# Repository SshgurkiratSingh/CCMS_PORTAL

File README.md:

# CCMS Portal — Centralized Command & Monitoring System

A full-stack smart streetlight fleet management system with real-time monitoring, remote control, and analytics. This monorepo contains the Next.js operator console, native Android mobile application, AWS Lambda backend, ESP32 firmware for edge devices, and PCB designs.

## Screenshots & Assets

| Fleet Info | Node Info | Command Menu |
|:---:|:---:|:---:|
|  |  |  |

| Prototype | Power Supply Unit | Offsite Interface Card |
|:---:|:---:|:---:|
|  |  |  |

---

## Architecture Overview

```text
┌──────────────────┐       ┌──────────────┐       ┌─────────────────┐
│ RPi Gateway + STM│──────▶│   AWS IoT    │──────▶│  SQS → Lambda   │──────▶ DynamoDB
│  (streetlights)  │  MQTT │   Core       │       │ (saveDataFromSQ)│
└──────────────────┘       └──────────────┘       └─────────────────┘
                                                          │
                                                          ▼
┌──────────────────┐       ┌──────────────┐       ┌─────────────────┐
│   Next.js App    │◀──────│   Lambda     │◀──────│  DynamoDB       │
│  (operator       │  REST │   API        │       │                 │
│   console)       │       │   Gateway    │       │                 │
└──────────────────┘       └──────────────┘       └─────────────────┘
         ▲                        ▲
         │                        │
         └─────────┬──────────────┘
                   │ REST (x-dashboard-key / x-admin-key)
                   ▼
        ┌────────────────────┐
        │    Android App     │
        │  (CCMS Mobile Console)│
        └────────────────────┘
```

### Components

| Layer                             | Technology                            | Location                                                         |
| --------------------------------- | ------------------------------------- | ---------------------------------------------------------------- |
| **Web Portal**                    | Next.js 16, React 19, Tailwind CSS v4 | [`Frontend/ccms/`](./Frontend/ccms)                              |
| **Android App**                   | Kotlin, Jetpack Compose, Material 3, Retrofit | [`androidAPp/`](./androidAPp)                             |
| **Backend API**                   | Python AWS Lambda                     | [`Backend/Lambda/`](./Backend/Lambda)                            |
| **Firmware (RPi Gateway)**        | Python 3                              | [`Firmware/RPi_Gateway/`](./Firmware/RPi_Gateway)                |
| **Firmware (STM32 Node)**         | C++ (PlatformIO), STM32               | [`Firmware/STM32_Peripheral/`](./Firmware/STM32_Peripheral)      |
| **Firmware v2.0**                 | C++ (PlatformIO), ESP32               | [`Firmware/ESP32_wifi_CCMS_v2.0/`](./Firmware/ESP32_wifi_CCMS_v2.0) |
| **Firmware v2.0 (Pi link)**       | C++ (PlatformIO), ESP32               | [`Firmware/ESP32_wifi_CCMS_v2.0_PI_link/`](./Firmware/ESP32_wifi_CCMS_v2.0_PI_link) |
| **Firmware v1.0**                 | C++ (PlatformIO), ESP32               | [`Firmware/ESP32_wifi_CCMS_v1.0/`](./Firmware/ESP32_wifi_CCMS_v1.0) |
| **Hardware**                      | PCB Designs                           | [`Hardware/PCB Designs/`](./Hardware/PCB%20Designs)              |
| **Documentation**                 | MkDocs (Material theme)               | [`docs/`](./docs), [`mkdocs.yml`](./mkdocs.yml)                  |

---

## Android App — Mobile Command Console (`androidAPp/`)

A high-performance Android mobile application built with **Kotlin** and **Jetpack Compose (Material 3)** for real-time fleet monitoring, remote relay dispatch, and telemetry analytics.

### Key Features

- 📊 **Command Center Dashboard**: Fleet-wide HUD showing active nodes, active alarms, grid voltage ($V$), frequency ($Hz$), system power factor ($PF$), and instantaneous load ($kW$).
- ⚡ **Node Fleet Browser**: Filter and search panels by Panel ID, location, or MAC address with direct relay switch toggling and optimistic UI state updates.
- 🔍 **Live Schneider Modbus Telemetry**: Real-time readout of Schneider Electric energy meter registers (`R3027`, `R3035`, `R3109`, `R3059`, `R3053`, `R3009`, `R3083`), diagnostic battery voltage, mains status, and enclosure temperature.
- 🚨 **Automated Telemetry Fault Detection Engine**: Runs 6 continuous telemetry analysis rules:
  - **E001**: Sustained Low Voltage ($< 200\text{V}$)
  - **E002**: Sustained High Voltage Spike ($> 250\text{V}$)
  - **E003**: Power Factor Degradation ($< 0.75$)
  - **E004**: Grid Frequency Instability ($< 49.5\text{Hz}$ or $> 50.5\text{Hz}$)
  - **E006/E007**: Temperature Breach ($> 50^\circ\text{C}$ or $> 65^\circ\text{C}$)
  - **E008**: Enclosure Tamper / Tilt Switch Triggered
- 🗺️ **Map Location Integration**: Tap location pins to launch Google Maps pointing to exact GPS coordinates ($30.7356^\circ\text{N}, 76.7105^\circ\text{E}$).
- 📈 **Interactive Telemetry Line Charts**: Canvas-drawn time-series graphs with touch cursor inspection and range selectors (1h, 6h, 24h, 7d).
- ⚙️ **Dual-Key API Gateway Config**: Configure AWS Lambda endpoint, Level 1 Dashboard key (`x-dashboard-key`), Level 2 Admin key (`x-admin-key`), and toggle offline simulator mode.

### Tech Stack

- **Language**: Kotlin 2.2
- **UI Framework**: Jetpack Compose, Material 3, Navigation Compose
- **Networking**: Retrofit 2.11, OkHttp 4.12, Gson
- **Async State**: Kotlin Coroutines, StateFlow, ViewModel
- **Theme**: High-contrast Cyber Command Slate palette with Frosted Glassmorphism (`GlassCard`)

### Build & Export APK

```bash
cd androidAPp
./gradlew app:assembleDebug app:assembleRelease
```

#### Generated APK Paths

- **Debug APK**: [`androidAPp/app/build/outputs/apk/debug/app-debug.apk`](file:///home/gurkirat/Projects/CCMS_PORTAL/androidAPp/app/build/outputs/apk/debug/app-debug.apk)
- **Release APK**: [`androidAPp/app/build/outputs/apk/release/app-release-unsigned.apk`](file:///home/gurkirat/Projects/CCMS_PORTAL/androidAPp/app/build/outputs/apk/release/app-release-unsigned.apk)

---

## Frontend — Operator Console (`Frontend/ccms/`)

A Next.js static export application that provides a real-time operations dashboard for managing streetlight fleets.

### Pages

| Route                   | Description                                                                    |
| ----------------------- | ------------------------------------------------------------------------------ |
| `/`                   | Landing page with login / dashboard links                                      |
| `/login`              | Authenticate using Dashboard Key and Admin Key                                 |
| `/dashboard`          | Fleet-wide summary (panel count, active alarms, grid metrics, energy estimate) |
| `/panels`             | Browse, filter, and search all panels (map + list views)                       |
| `/panel?id={panelId}` | Live status, telemetry charts, command dispatch (relay, schedule, shadow keys) |
| `/manage-panel`       | Register new panels with GPS coordinates                                       |
| `/analytics`          | Historical telemetry viewer with date range filtering                          |
| `/alerts`             | Active alerts list with severity filtering and acknowledgment                  |

### Key Technologies

- **Framework**: Next.js 16 (`output: "export"` — fully static, no server functions)
- **UI Library**: HeroUI v3, Lucide icons
- **Charts**: Recharts (telemetry time-series)
- **Maps**: Leaflet + React-Leaflet (panel fleet locations, location picker)
- **Styling**: Tailwind CSS v4, Framer Motion (animations)
- **Auth**: API keys stored in `localStorage`, sent as `x-dashboard-key` / `x-admin-key` headers

### Environment Variables

```env
NEXT_PUBLIC_API_BASE_URL=https://85siwerqrg.execute-api.us-east-1.amazonaws.com/default/
```

Copy `Frontend/ccms/.env.example` → `Frontend/ccms/.env.local` and fill in real values.

### Run Locally

```bash
cd Frontend/ccms
npm install
npm run dev       # development server at http://localhost:3000
npm run build     # static export to Frontend/ccms/out/
```

---

## Backend — AWS Lambda (`Backend/Lambda/`)

Python-based serverless functions deployed behind API Gateway.

### Functions

| File                                                         | Purpose                                                                            |
| ------------------------------------------------------------ | ---------------------------------------------------------------------------------- |
| [`lambdaAPI.py`](./Backend/Lambda/lambdaAPI.py)                       | REST API handler — serves dashboard snapshot, panel status, history, and commands |
| [`saveDataFromSQStoDB,py`](./Backend/Lambda/saveDataFromSQStoDB,py) | SQS-triggered function that writes incoming telemetry to DynamoDB                  |

### API Endpoints (via `DashboardAPIHandler`)

| Method    | Query / Body                                             | Description                                      |
| --------- | -------------------------------------------------------- | ------------------------------------------------ |
| `GET`   | `?enquiry=snapshot`                                    | Returns all panels with latest data and metadata |
| `GET`   | `?enquiry=history&panel_id=X&start=T&end=T`            | Historical telemetry for a panel                 |
| `POST`  | `{ panel_id, ... }`                                    | Register a new panel                             |
| `PATCH` | `{ panel_id, desired_state/schedule/shadowKeys, ... }` | Send commands to a panel                         |

### Test Endpoints

A Node.js test script is available at [`Backend/Lambda/TestEndpoints/getData.js`](./Backend/Lambda/TestEndpoints/getData.js) for manual API testing.

---

## Hardware — Edge Firmware

The project supports both ESP32-centric designs and a new hybrid Raspberry Pi + STM32 architecture.

| Variant                | Description                                                                 |
| ---------------------- | --------------------------------------------------------------------------- |
| **RPi Gateway**        | Python daemon acting as an IoT gateway, handling AWS IoT MQTT and Shadow.   |
| **STM32 Peripheral**   | Hard-realtime STM32 node for sensors and Modbus, reports to RPi Gateway.    |
| **v1.0 (ESP32)**       | Base implementation with WiFi, MQTT, and energy meter reading               |
| **v2.0 (ESP32)**       | Enhanced version with AWS IoT Core integration, relay control, OTA-ready    |
| **v2.0 PI Link (ESP32)** | Variant designed to communicate via Raspberry Pi for additional relay logic |

### Key Hardware Interfaces (RPi + STM32)

- **Raspberry Pi**: Network handling (WiFi/Ethernet), AWS IoT Core communication.
- **Serial (UART)**: Two-way communication between Pi and STM32 (Baud 115200).
- **Relay Control**: Managed by STM32 GPIO (`PA0`).
- **Modbus**: Read by STM32 via RS485 transceiver.

Build STM32 firmware with [PlatformIO](https://platformio.org/):

```bash
cd Firmware/STM32_Peripheral
pio run -t upload
```

---

## API Types

All frontend types are defined in [`Frontend/ccms/lib/api/types.ts`](./Frontend/ccms/lib/api/types.ts). Key models:

- **PanelRecord** — panel metadata, status, GPS coordinates
- **PanelLiveStatus** — real-time telemetry snapshot (voltage, current, power factor, frequency, battery, temperature, tilt)
- **TelemetryPoint** — historical data point matching live status fields
- **PanelCommandPayload** — `SET_MANUAL_STATE`, `UPDATE_RTC_SCHEDULE`, or `UPDATE_SHADOW_KEYS`
- **AlertRecord** — fault alerts with severity, status, acknowledgment tracking
- **DashboardSummary** — fleet-wide aggregate metrics

---

## Documentation

Full project documentation is built with [MkDocs](https://www.mkdocs.org/) using the Material theme.

```bash
pip install mkdocs-material
mkdocs serve       # local preview at http://127.0.0.1:8000
mkdocs gh-deploy   # publish to GitHub Pages
```

The documentation is auto-deployed via [GitHub Actions](https://github.com/settings/actions) on pushes to `main` that touch `docs/` or `mkdocs.yml`.

### Included Docs

- [Frontend & Lambda Report](./docs/frontend-lambda-project-report.md)
- [Web Portal Guide](./docs/web-portal.md)
- [Hardware (ESP32)](./docs/hardware.md)
- [Lambda Backend](./docs/lambda.md)

---

## CI / CD

| Workflow                                        | Trigger                         | Action                                    |
| ----------------------------------------------- | ------------------------------- | ----------------------------------------- |
| [`gh-pages.yml`](.github/workflows/gh-pages.yml) | Push to `main` (docs changes) | Builds and deploys MkDocs to GitHub Pages |

---

## Project Structure

```text
CCMS_PORTAL/
├── androidAPp/                        ← Native Android App (Jetpack Compose)
├── Frontend/
│   └── ccms/                          ← Next.js operator console
├── Backend/
│   └── Lambda/                        ← AWS Lambda backend
├── Firmware/
│   ├── RPi_Gateway/                   ← Raspberry Pi Python daemon
│   ├── STM32_Peripheral/              ← STM32 hardware controller
│   ├── ESP32_wifi_CCMS_v1.0/          ← Firmware v1.0
│   ├── ESP32_wifi_CCMS_v2.0/          ← Firmware v2.0
│   └── ESP32_wifi_CCMS_v2.0_PI_link/  ← Firmware v2.0 (Pi link variant)
├── Hardware/
│   └── PCB Designs/                   ← Hardware designs
├── docs/                          ← MkDocs documentation source
├── mkdocs.yml                     ← Documentation site configuration
└── .github/workflows/             ← CI/CD pipelines
```

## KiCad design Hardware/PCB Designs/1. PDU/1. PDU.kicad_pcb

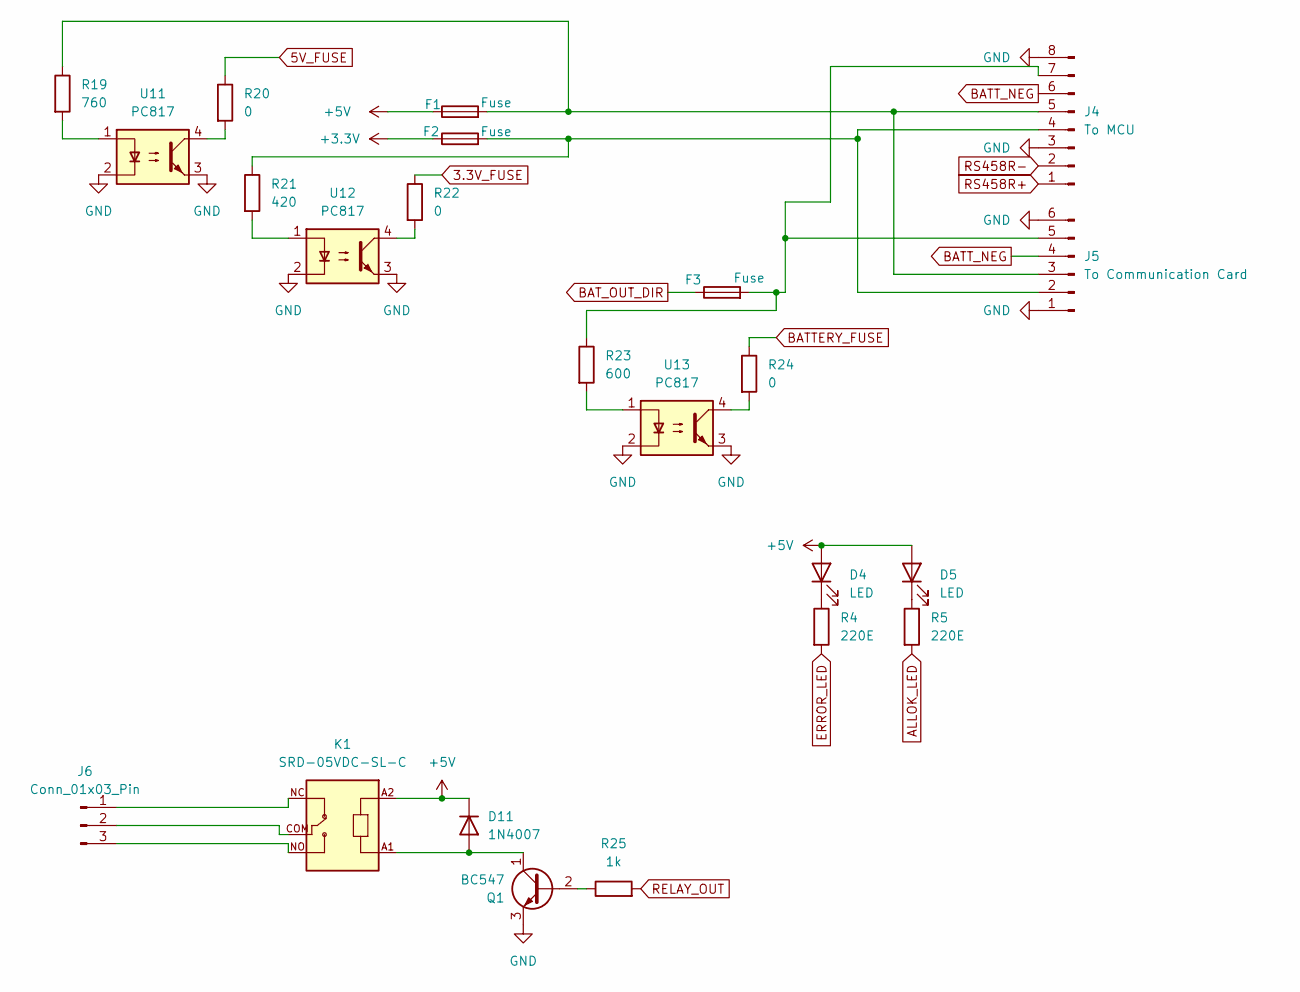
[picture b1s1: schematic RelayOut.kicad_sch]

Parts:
D4, D5: LED; LED_0402_1005Metric
D11: 1N4007; D_DO-41_SOD81_P10.16mm_Horizontal
F1, F2, F3: Fuse; Fuseholder_Blade_Mini_Keystone_3568
J4: To MCU; JST_XH_S8B-XH-A-1_1x08_P2.50mm_Horizontal
J5: To Communication Card; JST_XH_S6B-XH-A-1_1x06_P2.50mm_Horizontal
J6: Conn_01x03_Pin; PhoenixContact_MC_1,5_3-G-5.08_1x03_P5.08mm_Horizontal
K1: SRD-05VDC-SL-C; RELAY_SRD-05VDC-SL-C
Q1: BC547; TO-92_Inline
R4, R5: 220E; R_0805_2012Metric
R19: 760; R_0805_2012Metric
R20, R22, R24: 0; R_0805_2012Metric
R21: 420; R_0805_2012Metric
R23: 600; R_0805_2012Metric
R25: 1k; R_0805_2012Metric
U11, U12, U13: PC817; DIP-4_W7.62mm

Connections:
3.3V_FUSE: R22.1; also elsewhere on the board
5V_FUSE: R20.1; also elsewhere on the board
+3.3V: F2.1; also elsewhere on the board
+5V: D4.2 (A), D5.2 (A), D11.1 (K), F1.1, K1.A2; also elsewhere on the board
ALLOK_LED: R5.2; also elsewhere on the board
BATTERY_FUSE: R24.1; also elsewhere on the board
BATT_NEG: J4.6, J5.4; also elsewhere on the board
BAT_OUT_DIR: F3.1; also elsewhere on the board
ERROR_LED: R4.2; also elsewhere on the board
GND: J4.3, J4.8, J5.1, J5.6, Q1.3 (E), U11.2, U11.3, U12.2, U12.3, U13.2, U13.3; also elsewhere on the board
unnamed: D4.1 (K), R4.1
unnamed: D5.1 (K), R5.1
unnamed: D11.2 (A), K1.A1, Q1.1 (C)
unnamed: F2.2, J4.4, J5.2, R21.1
unnamed: F1.2, J4.5, J5.3, R19.1
unnamed: F3.2, J4.7, J5.5, R23.1
unnamed: J6.1, K1.NC
unnamed: J6.2, K1.COM
unnamed: J6.3, K1.NO
unnamed: Q1.2 (B), R25.1
unnamed: R19.2, U11.1
unnamed: R20.2, U11.4
unnamed: R21.2, U12.1
unnamed: R22.2, U12.4
unnamed: R23.2, U13.1
unnamed: R24.2, U13.4
RELAY_OUT: R25.2; also elsewhere on the board
RS458R+: J4.1; also elsewhere on the board
RS458R-: J4.2; also elsewhere on the board

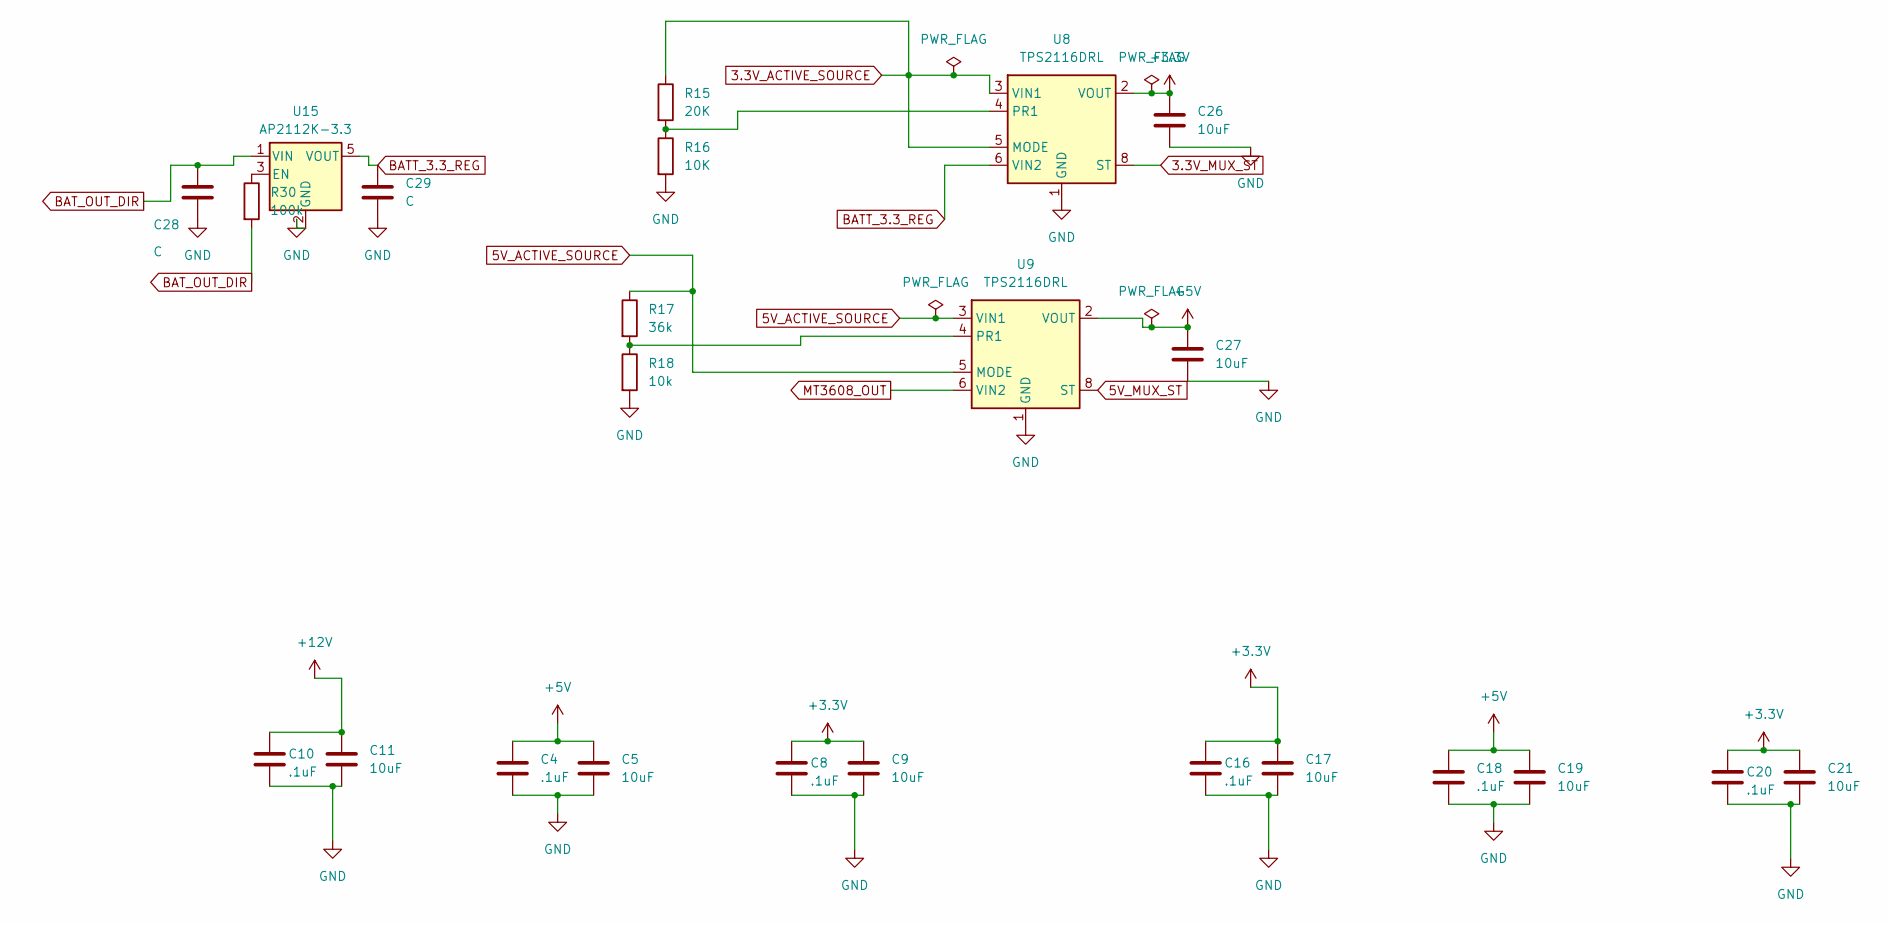
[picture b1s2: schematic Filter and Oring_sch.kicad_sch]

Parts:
C4, C8, C10, C16, C18, C20: .1uF; C_0805_2012Metric
C5, C9, C11, C17, C19, C21, C26, C27: 10uF; C_0805_2012Metric
C28, C29: C; C_0805_2012Metric
R15: 20K; R_0402_1005Metric
R16: 10K; R_0402_1005Metric
R17: 36k; R_0402_1005Metric
R18: 10k; R_0402_1005Metric
R30: 100k; R_0805_2012Metric
U8, U9: TPS2116DRL; SOT-583-8
U15: AP2112K-3.3; SOT-23-5

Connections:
3.3V_ACTIVE_SOURCE: R15.1, U8.3 (VIN1), U8.5 (MODE); also elsewhere on the board
3.3V_MUX_ST: U8.8 (ST); also elsewhere on the board
5V_ACTIVE_SOURCE: R17.1, U9.3 (VIN1), U9.5 (MODE); also elsewhere on the board
5V_MUX_ST: U9.8 (ST); also elsewhere on the board
+3.3V: C8.1, C9.1, C16.1, C17.1, C20.1, C21.1, C26.1, U8.2 (VOUT), U8.7 (VOUT); also elsewhere on the board
+5V: C4.1, C5.1, C18.1, C19.1, C27.1, U9.2 (VOUT), U9.7 (VOUT); also elsewhere on the board
+12V: C10.1, C11.1; also elsewhere on the board
BATT_3.3_REG: C29.1, U8.6 (VIN2), U15.5 (VOUT)
BAT_OUT_DIR: C28.1, R30.2, U15.1 (VIN); also elsewhere on the board
GND: C4.2, C5.2, C8.2, C9.2, C10.2, C11.2, C16.2, C17.2, C18.2, C19.2, C20.2, C21.2, C26.2, C27.2, C28.2, C29.2, R16.2, R18.2, U8.1 (GND), U9.1 (GND), U15.2 (GND); also elsewhere on the board
MT3608_OUT: U9.6 (VIN2); also elsewhere on the board
unnamed: R15.2, R16.1, U8.4 (PR1)
unnamed: R17.2, R18.1, U9.4 (PR1)
unnamed: R30.1, U15.3 (EN)

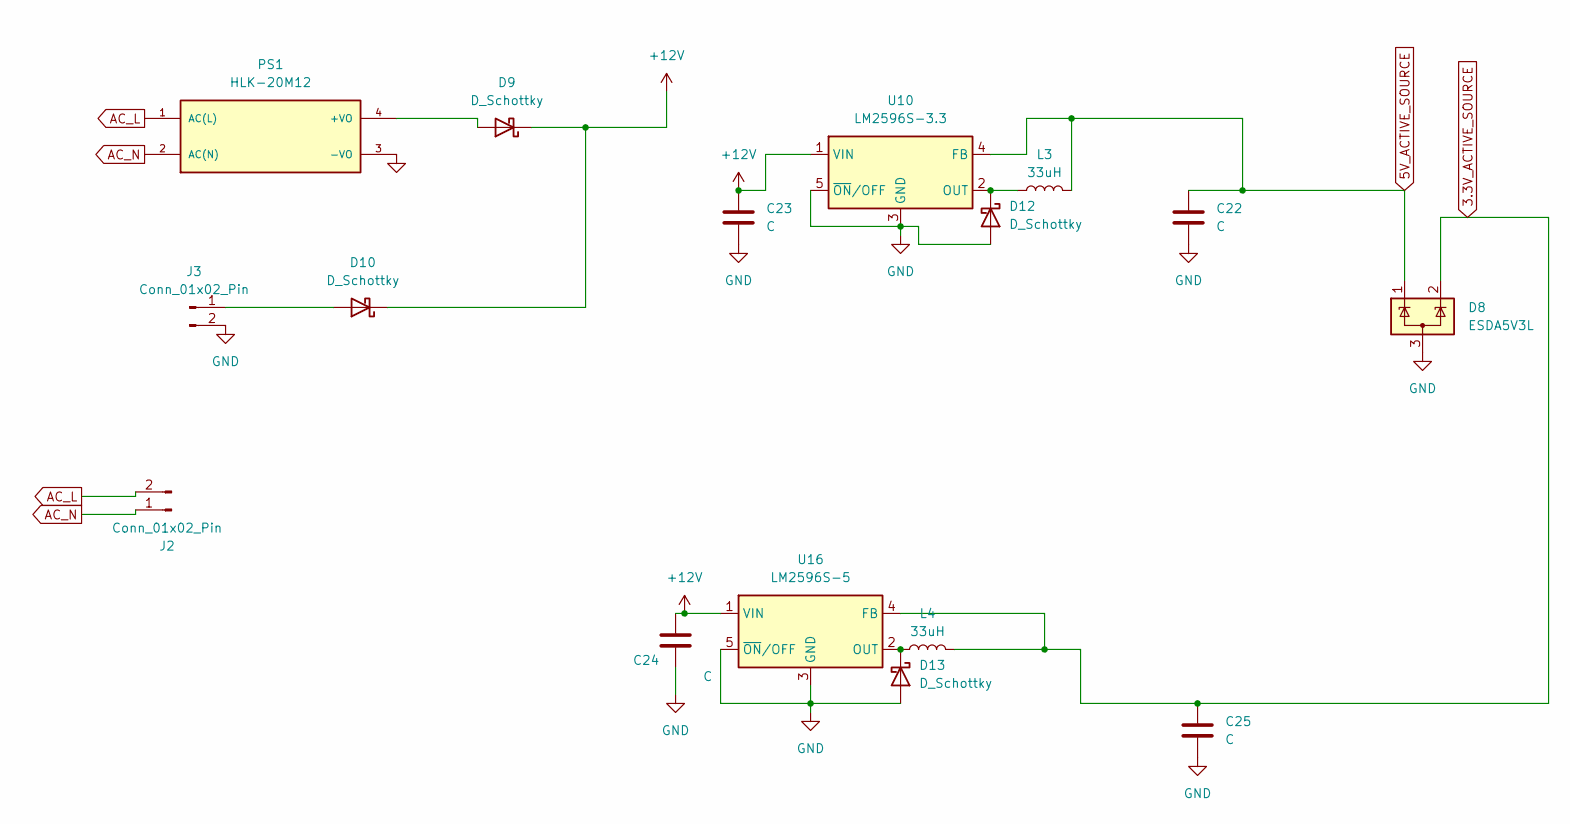
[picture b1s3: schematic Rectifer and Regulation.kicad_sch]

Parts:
C22, C23, C24, C25: C; C_0805_2012Metric
D8: ESDA5V3L; SOT-23-3
D9, D10: D_Schottky; D_SMC_Handsoldering
D12, D13: D_Schottky; D_3220_8050Metric
J2: Conn_01x02_Pin; PhoenixContact_MSTB_2,5_2-GF_1x02_P5.00mm_Horizontal_Thread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
J3: Conn_01x02_Pin; Molex_KK-254_AE-6410-02A_1x02_P2.54mm_Vertical
L3, L4: 33uH; L_10.4x10.4_H4.8
PS1: HLK-20M12; CONV_HLK-20M12; PARTREV V1.3
U10: LM2596S-3.3; TO-263-5_TabPin3
U16: LM2596S-5; TO-263-5_TabPin3

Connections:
3.3V_ACTIVE_SOURCE: C25.1, D8.2 (K), L4.2, U16.4 (FB); also elsewhere on the board
5V_ACTIVE_SOURCE: C22.1, D8.1 (K), L3.2, U10.4 (FB); also elsewhere on the board
+12V: C23.1, C24.1, D9.1 (K), D10.1 (K), U10.1 (VIN), U16.1 (VIN); also elsewhere on the board
AC_L: J2.2, PS1.1 (AC(L))
AC_N: J2.1, PS1.2 (AC(N))
GND: C22.2, C23.2, C24.2, C25.2, D8.3 (A), D12.2 (A), D13.2 (A), J3.2, PS1.3 (-VO), U10.3 (GND), U10.5 (~ON/OFF), U16.3 (GND), U16.5 (~ON/OFF); also elsewhere on the board
unnamed: D9.2 (A), PS1.4 (+VO)
unnamed: D10.2 (A), J3.1
unnamed: D12.1 (K), L3.1, U10.2 (OUT)
unnamed: D13.1 (K), L4.1, U16.2 (OUT)

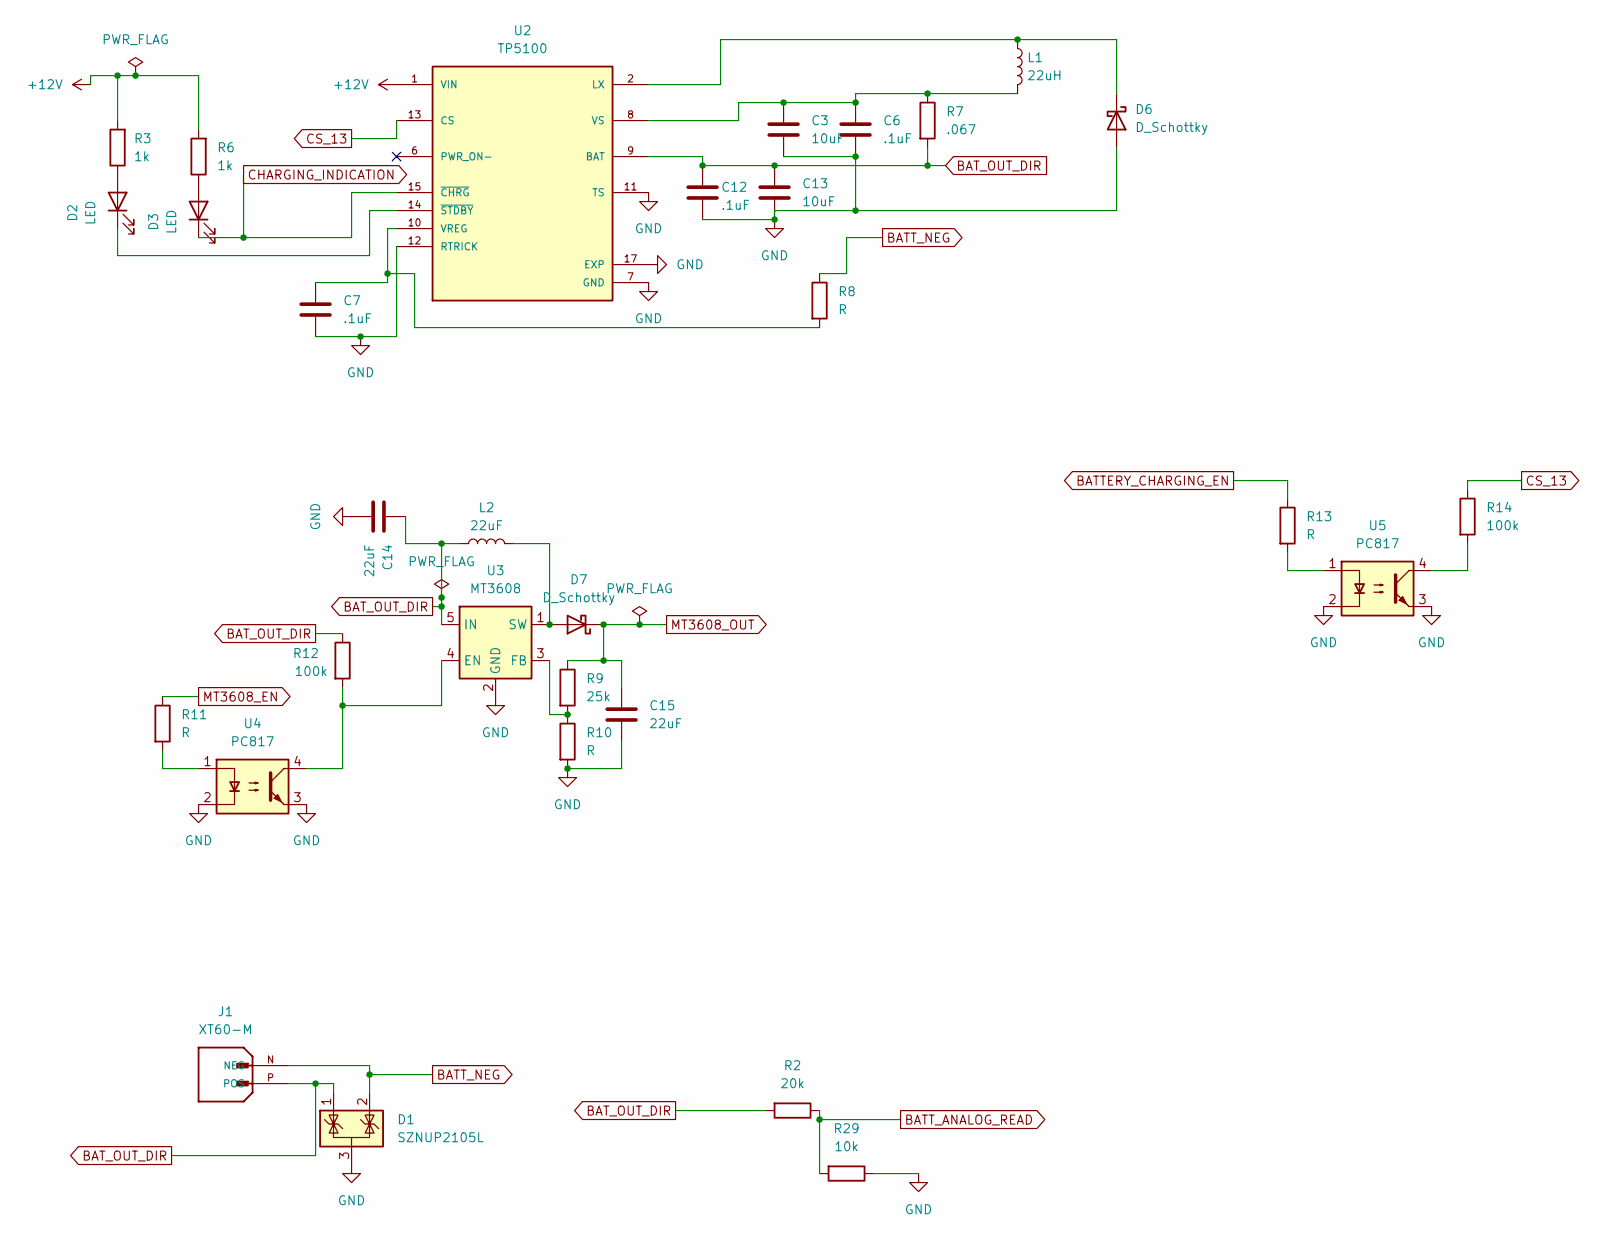
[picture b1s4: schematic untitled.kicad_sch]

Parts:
C3, C13: 10uF; C_0805_2012Metric
C6, C7, C12: .1uF; C_0805_2012Metric
C14, C15: 22uF; C_0805_2012Metric
D1: SZNUP2105L; SOT-23
D2, D3: LED; LED_0805_2012Metric
D6: D_Schottky; D_SMA
D7: D_Schottky; D_0805_2012Metric
J1: XT60-M; AMASS_XT60-M; PARTREV V1.2
L1: 22uH; L_Bourns-SRN6028
L2: 22uF; L_Coilcraft_XAL6060-XXX
R2: 20k; R_0805_2012Metric
R3, R6: 1k; R_0805_2012Metric
R7: .067; R_1206_3216Metric
R8, R10, R11, R13: R; R_0805_2012Metric
R9: 25k; R_0612_1632Metric_Pad1.18x3.40mm_HandSolder
R12, R14: 100k; R_0805_2012Metric
R29: 10k; R_0805_2012Metric
U2: TP5100; QFN65P400X400X90-17N; PARTREV 2.3
U3: MT3608; SOT-23-6
U4, U5: PC817; DIP-4_W7.62mm

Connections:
+12V: R3.2, R6.2, U2.1 (VIN), U2.4 (VIN), U2.5 (VIN), U2.16 (VIN); also elsewhere on the board
BATTERY_CHARGING_EN: R13.1; also elsewhere on the board
BATT_ANALOG_READ: R2.1, R29.2; also elsewhere on the board
BATT_NEG: D1.2 (K), J1.N (NEG), R8.1; also elsewhere on the board
BAT_OUT_DIR: C12.1, C13.1, C14.1, D1.1 (K), J1.P (POS), L2.1, R2.2, R7.2, R12.1, U2.9 (BAT), U3.5 (IN); also elsewhere on the board
CHARGING_INDICATION: D3.1 (K), U2.15 (~CHRG); also elsewhere on the board
CS_13: R14.1, U2.13 (CS)
GND: C3.2, C6.2, C7.2, C12.2, C13.2, C14.2, C15.2, D1.3 (A), D6.2 (A), R10.2, R29.1, U2.7 (GND), U2.11 (TS), U2.12 (RTRICK), U2.17 (EXP), U3.2 (GND), U4.2, U4.3, U5.2, U5.3; also elsewhere on the board
MT3608_EN: R11.1; also elsewhere on the board
MT3608_OUT: C15.1, D7.1 (K), R9.1; also elsewhere on the board
unnamed: D2.2 (A), R3.1
unnamed: D2.1 (K), U2.14 (~STDBY)
unnamed: D3.2 (A), R6.1
unnamed: D6.1 (K), L1.1, U2.2 (LX), U2.3 (LX)
unnamed: D7.2 (A), L2.2, U3.1 (SW)
unnamed: R11.2, U4.1
unnamed: R13.2, U5.1
unnamed: R14.2, U5.4
unnamed: C7.1, R8.2, U2.10 (VREG)
unnamed: C3.1, C6.1, L1.2, R7.1, U2.8 (VS)
unnamed: R12.2, U3.4 (EN), U4.4
unnamed: R9.2, R10.1, U3.3 (FB)

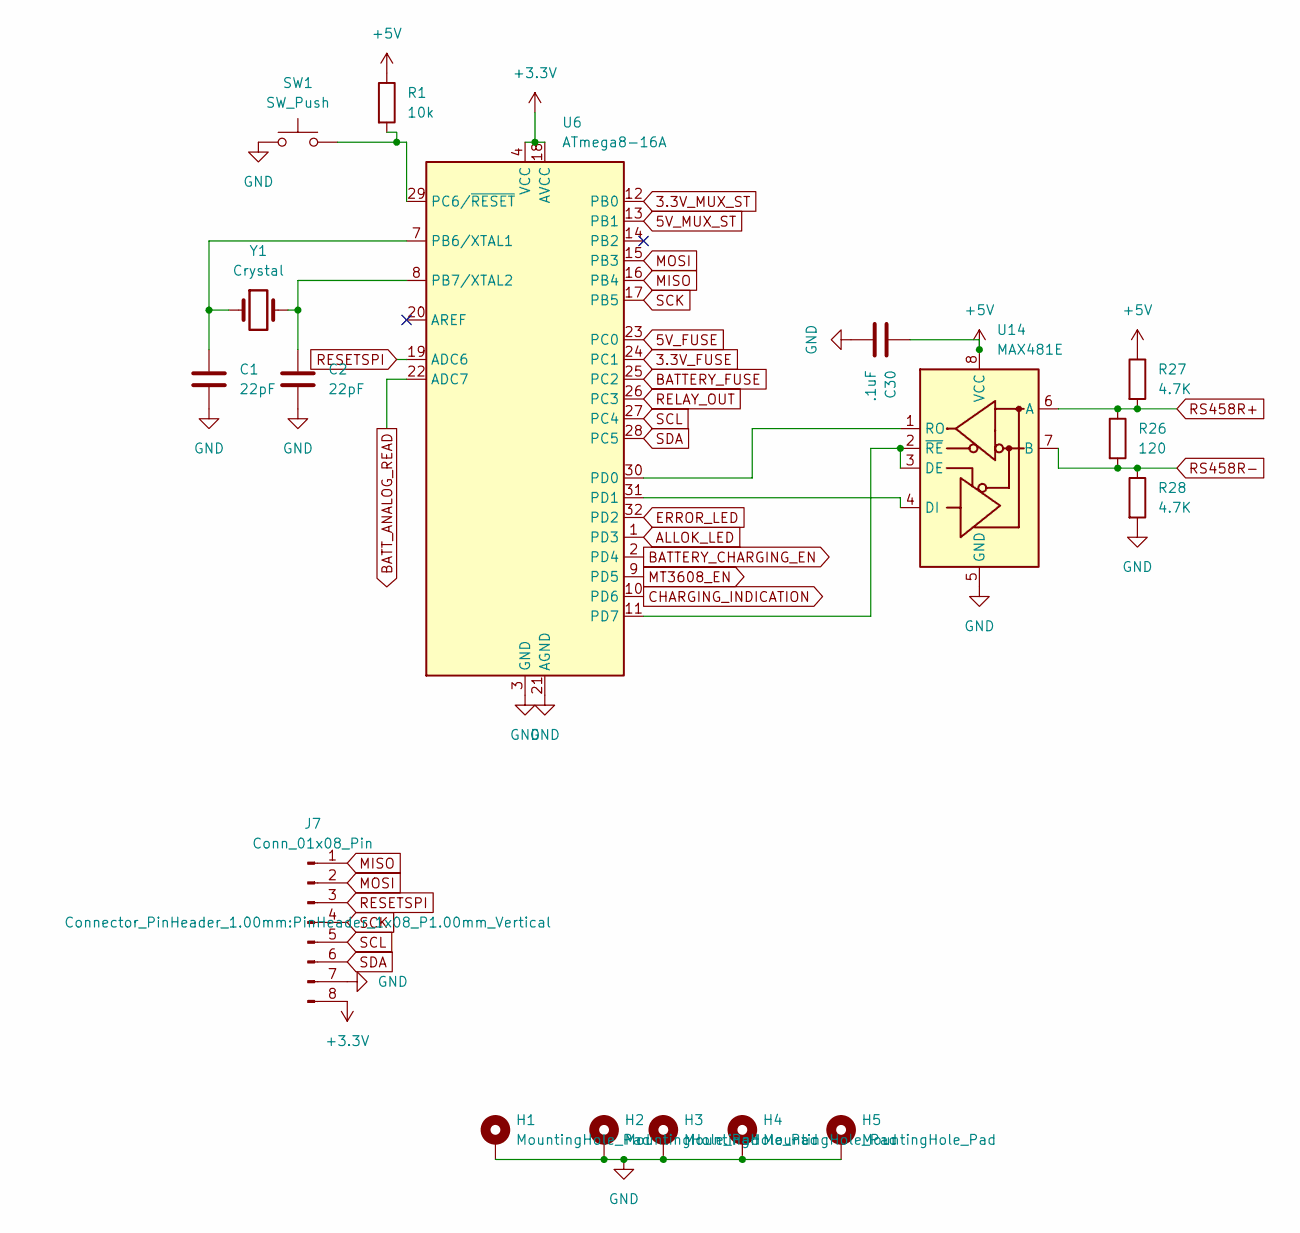
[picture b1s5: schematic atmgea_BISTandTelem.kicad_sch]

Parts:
C1, C2: 22pF; C_0805_2012Metric
C30: .1uF; C_0805_2012Metric
H1, H2, H3, H4, H5: MountingHole_Pad; MountingHole_3.2mm_M3_ISO7380_Pad
J7: Conn_01x08_Pin; PinHeader_1x08_P1.00mm_Vertical
R1: 10k; R_0805_2012Metric
R26: 120; R_0402_1005Metric
R27, R28: 4.7K; R_0805_2012Metric
SW1: SW_Push; SW_PUSH_6mm
U6: ATmega8-16A; TQFP-32_7x7mm_P0.8mm
U14: MAX481E; SOIC-8_3.9x4.9mm_P1.27mm
Y1: Crystal; Crystal_HC49-U_Vertical

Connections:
3.3V_FUSE: U6.24 (PC1); also elsewhere on the board
3.3V_MUX_ST: U6.12 (PB0); also elsewhere on the board
5V_FUSE: U6.23 (PC0); also elsewhere on the board
5V_MUX_ST: U6.13 (PB1); also elsewhere on the board
+3.3V: J7.8, U6.4 (VCC), U6.6 (VCC), U6.18 (AVCC); also elsewhere on the board
+5V: C30.1, R1.1, R27.1, U14.8 (VCC); also elsewhere on the board
ALLOK_LED: U6.1 (PD3); also elsewhere on the board
BATTERY_CHARGING_EN: U6.2 (PD4); also elsewhere on the board
BATTERY_FUSE: U6.25 (PC2); also elsewhere on the board
BATT_ANALOG_READ: U6.22 (ADC7); also elsewhere on the board
CHARGING_INDICATION: U6.10 (PD6); also elsewhere on the board
ERROR_LED: U6.32 (PD2); also elsewhere on the board
GND: C1.2, C2.2, C30.2, H1.1 (1_1), H2.1 (1_1), H3.1 (1_1), H4.1 (1_1), H5.1 (1_1), J7.7, R28.2, SW1.1, U6.3 (GND), U6.5 (GND), U6.21 (AGND), U14.5 (GND); also elsewhere on the board
MISO: J7.1, U6.16 (PB4)
MOSI: J7.2, U6.15 (PB3)
MT3608_EN: U6.9 (PD5); also elsewhere on the board
unnamed: C1.1, U6.7 (PB6/XTAL1), Y1.1
unnamed: C2.1, U6.8 (PB7/XTAL2), Y1.2
unnamed: R1.2, SW1.2, U6.29 (PC6/~RESET)
unnamed: U6.11 (PD7), U14.2 (~RE), U14.3 (DE)
unnamed: U6.31 (PD1), U14.4 (DI)
unnamed: U6.30 (PD0), U14.1 (RO)
RELAY_OUT: U6.26 (PC3); also elsewhere on the board
RESETSPI: J7.3, U6.19 (ADC6)
RS458R+: R26.1, R27.2, U14.6 (A); also elsewhere on the board
RS458R-: R26.2, R28.1, U14.7 (B); also elsewhere on the board
SCK: J7.4, U6.17 (PB5)
SCL: J7.5, U6.27 (PC4)
SDA: J7.6, U6.28 (PC5)

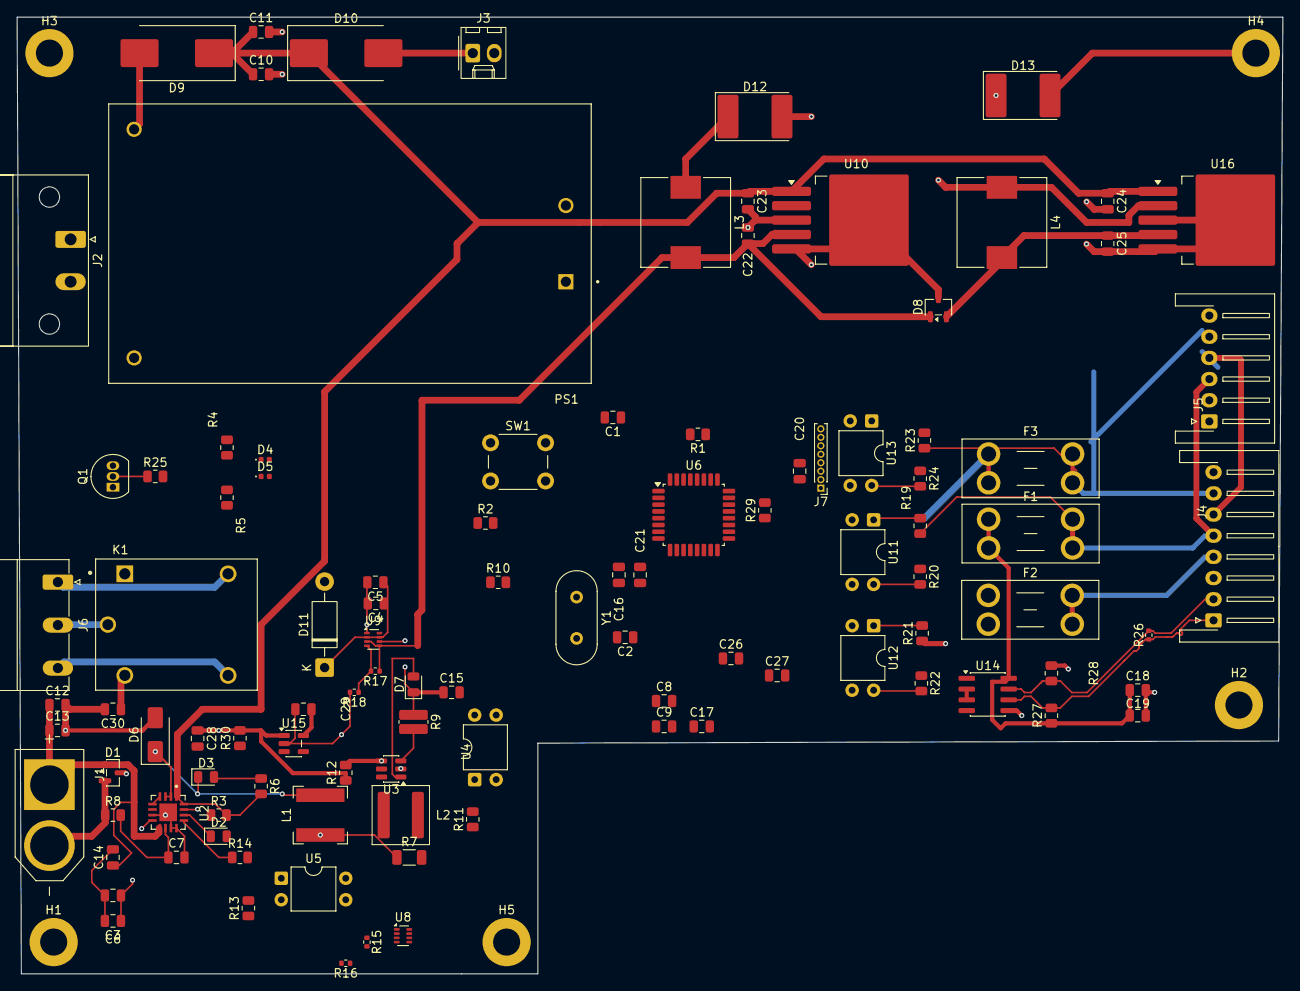
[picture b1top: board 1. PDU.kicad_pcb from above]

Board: 4 copper layers, 149.5 x 113.0 mm, 111 parts (0 on the bottom side), 74 nets.

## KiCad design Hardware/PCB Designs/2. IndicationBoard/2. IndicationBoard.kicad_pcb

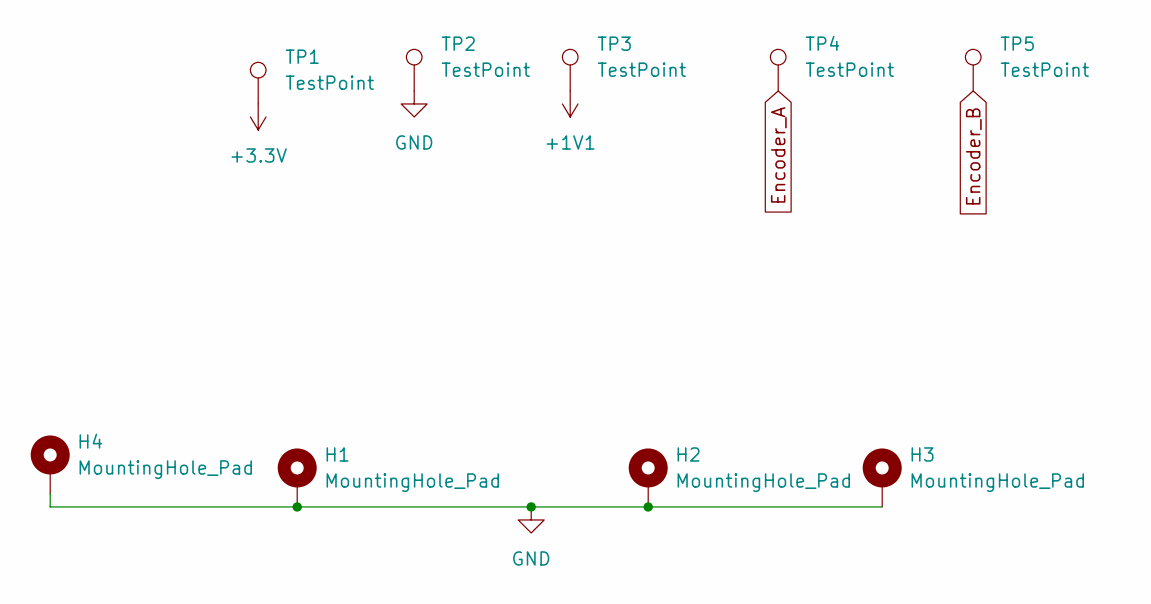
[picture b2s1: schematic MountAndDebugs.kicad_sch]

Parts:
H1, H2, H3, H4: MountingHole_Pad; MountingHole_2.2mm_M2_ISO7380_Pad
TP1, TP2, TP3, TP4, TP5: TestPoint; TestPoint_Pad_2.5x2.5mm

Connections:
+1V1: TP3.1; also elsewhere on the board
+3.3V: TP1.1; also elsewhere on the board
Encoder_A: TP4.1; also elsewhere on the board
Encoder_B: TP5.1; also elsewhere on the board
GND: H1.1, H2.1, H3.1, H4.1, TP2.1; also elsewhere on the board

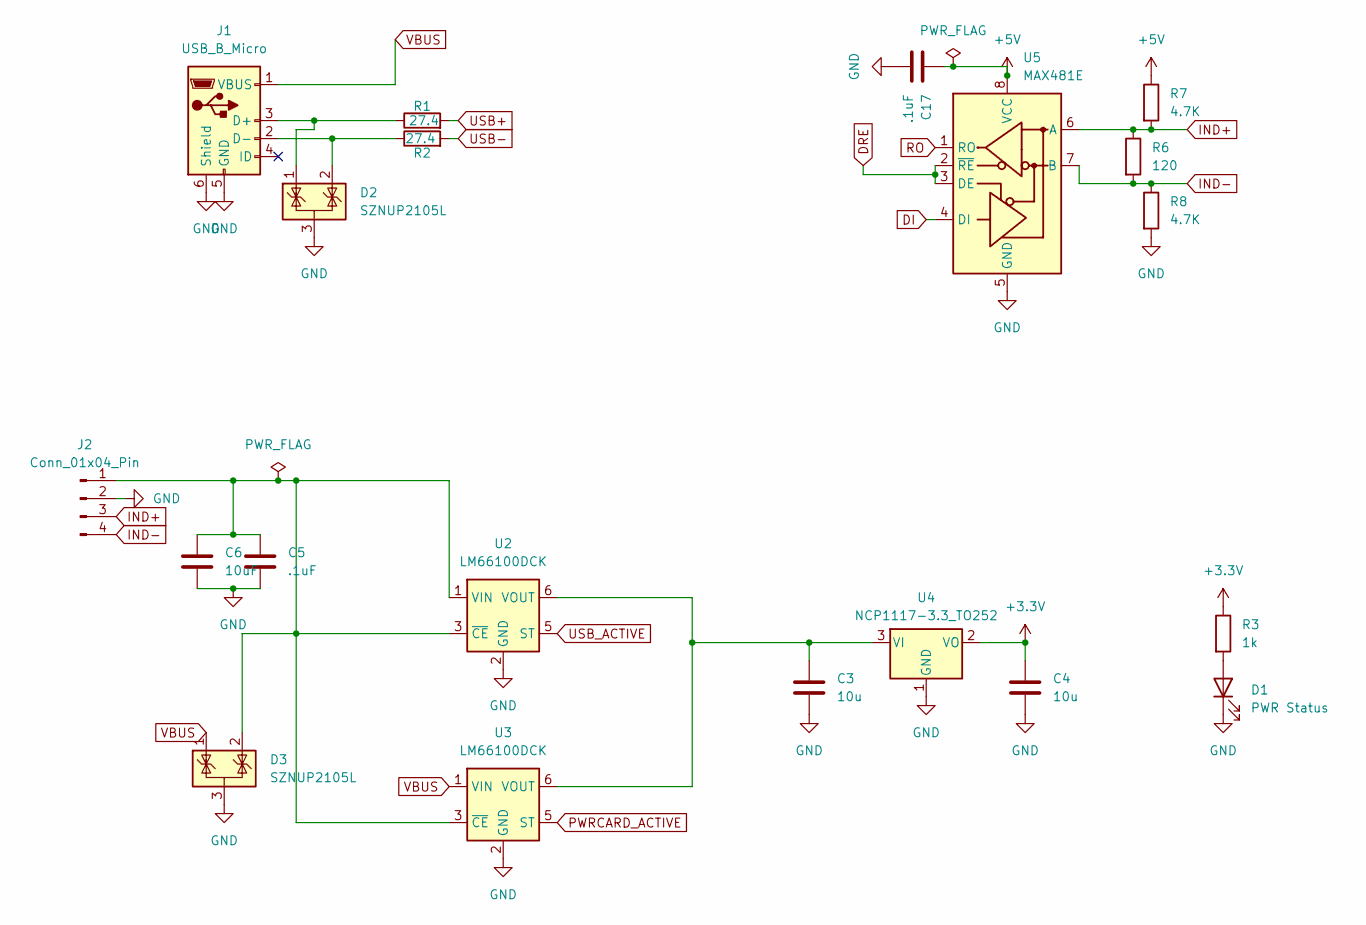
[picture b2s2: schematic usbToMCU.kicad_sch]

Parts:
C3, C4: 10u; C_0402_1005Metric
C5: .1uF; C_0402_1005Metric
C6: 10uF; C_0402_1005Metric
C17: .1uF; C_0805_2012Metric
D1: PWR Status; LED_0402_1005Metric_Pad0.77x0.64mm_HandSolder
D2, D3: SZNUP2105L; SOT-23
J1: USB_B_Micro; USB_Micro-B_Molex_47346-0001
J2: Conn_01x04_Pin; JST_PH_S4B-PH-K_1x04_P2.00mm_Horizontal
R1, R2: 27.4; R_0402_1005Metric
R3: 1k; R_0402_1005Metric
R6: 120; R_0402_1005Metric
R7, R8: 4.7K; R_0805_2012Metric
U2, U3: LM66100DCK; SOT-363_SC-70-6
U4: NCP1117-3.3_TO252; TO-252-2
U5: MAX481E; SOIC-8_3.9x4.9mm_P1.27mm

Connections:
+3.3V: C4.1, R3.1, U4.2 (VO); also elsewhere on the board
+5V: C17.1, R7.1, U5.8 (VCC)
DI: U5.4 (DI); also elsewhere on the board
DRE: U5.2 (~RE), U5.3 (DE); also elsewhere on the board
GND: C3.2, C4.2, C5.2, C6.2, C17.2, D1.1 (K), D2.3 (A), D3.3 (A), J1.5 (GND), J1.6 (Shield), J2.2, R8.2, U2.2 (GND), U3.2 (GND), U4.1 (GND), U5.5 (GND); also elsewhere on the board
IND+: J2.3, R6.1, R7.2, U5.6 (A)
IND-: J2.4, R6.2, R8.1, U5.7 (B)
unnamed: D1.2 (A), R3.2
unnamed: D2.1 (K), J1.3 (D+), R1.1
unnamed: D2.2 (K), J1.2 (D-), R2.1
unnamed: C5.1, C6.1, D3.2 (K), J2.1, U2.1 (VIN), U2.3 (~CE), U3.3 (~CE)
unnamed: C3.1, U2.6 (VOUT), U3.6 (VOUT), U4.3 (VI)
PWRCARD_ACTIVE: U3.5 (ST); also elsewhere on the board
RO: U5.1 (RO); also elsewhere on the board
USB+: R1.2; also elsewhere on the board
USB-: R2.2; also elsewhere on the board
USB_ACTIVE: U2.5 (ST); also elsewhere on the board
VBUS: D3.1 (K), J1.1 (VBUS), U3.1 (VIN)
